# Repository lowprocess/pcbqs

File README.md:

# pcbqs

PCB DC/power-integrity analysis, magneto-quasistatic and PEEC extraction, magnetic
near fields, low-frequency S-parameters, and ngspice operational circuits with
passive copper feedback.

```sh
pip install .
python -m pcbqs.pdn --describe --json
python -m pcbqs.mqs --describe --json
python -m pcbqs.sparams board.kicad_pcb --fmin 1e3 --fmax 1e8 --out lf
python -m pcbqs.circuit --template boost > boost.json
python -m pcbqs.circuit boost.json --out result
python -m pcbqs.circuit src/pcbqs/data/wpthb_bridge.json --out wpthb               # the wpthb full bridge
```

JSON-based solving, layout/mesh export and field reconstruction work without
`mom25d` or `kicad2ems`. Install `.[kicad2ems]` to import `.kicad_pcb` files.

With kicad2ems installed the four tools are its analyses (`pcbqs/analyses.py`, the
`kicad2ems.analyses` entry points) and `pcbqs.sparams` one of its S-parameter solvers
(`kicad2ems.solvers`: `--solvers pcbqs`): `kicad2ems --check` lists them, a config keeps a
study's under `[analysis]`, and kicad2ems-gui builds each one's settings from its
options table, runs it and shows what its result folder holds: the maps as field
dumps in its Viewer, the report and the curves (`pcbqs/reports.py`) on its Results
page. The circuit examples are configs beside their models
(`circuit/examples/*.toml`), under its File > Examples > Circuits.
Install ngspice separately for operational circuits. Component models and
parasitics are explicit assumptions; footprints do not imply calibrated models.

On Python versions without a sufficiently recent Triangle wheel (including
Python 3.14), use the kicad2ems installer: its QS option builds the pinned mesher
with the floating-point flags required by Triangle's exact predicates.

The optional CPU backend is built with `pip install '.[core]'` followed by
`python -m pcbqs.core.build`. NumPy/threaded fallbacks remain available. CuPy GPU
fill is optional: select a matching CUDA/ROCm extra and `--fill-backend cupy`.
Execution controls use `PCBQS_FILL_BACKEND`, `PCBQS_FILL_THREADS`,
`PCBQS_OMP_THREADS`, `PCBQS_NO_CORE` and `PCBQS_ARCH`; general OpenMP settings
remain supported. Static-fill plugins use the `pcbqs.static_backends` entry group.

- [Quasistatic guide](docs/quasistatic.md)
- [Low-frequency S-parameters](docs/sparams.md): a board's ports from DC to a tenth of a wavelength, with the
  return current where it flows; `--solvers pcbqs` in a kicad2ems run. Its example,
  `examples/return-path/return_path.py`: what a ground via's place does to a layer change
- [Circuits](docs/circuit.md): any circuit of parts, nodes and drives, by ngspice: its parts' losses for the
  thermal analysis, its copper's currents for the fields; ten examples, each with a board whose copper can be put in, and the wpthb full bridge; KiCad boards,
  schematics and netlists read into a model
- [Temperature](docs/thermal.md): a trial of a lightweight thermal solver, on a grid and on the triangle mesh
- [Validation and limits](docs/quasistatic-validation.md)
- [Migration](docs/migration.md)
- [Copied-code provenance](PROVENANCE.json)
- [PEEC and skin-effect test PCB](examples/peec-skin/README.md): two coupons,
  model comparisons, independent references and a reproducible KiCad layout.
- [Experimental PEEC PDN comparison](examples/pdn-peec-trial/README.md):
  loaded rails, independent DC/AC references, and mesh sensitivity.
- [Jetson AGX Thor PDN check](examples/jetson-pdn/REPORT.md): a real-board DC
  cross-check, cavity limitations, and a bounded local PEEC/skin comparison.
- [PEEC memory reduction](examples/peec-memory/REPORT.md) and the
  [experimental compressed backend](docs/peec-memory.md): graded meshes,
  hierarchical current/charge operators and iterative solving.

Private `_numerics` functions are independently maintained snapshots, not a
shared library or a runtime link to MoM. `emsdev` supplies only existing hardware
and native-build services. RF/full-wave solvers remain in `mom25d`.

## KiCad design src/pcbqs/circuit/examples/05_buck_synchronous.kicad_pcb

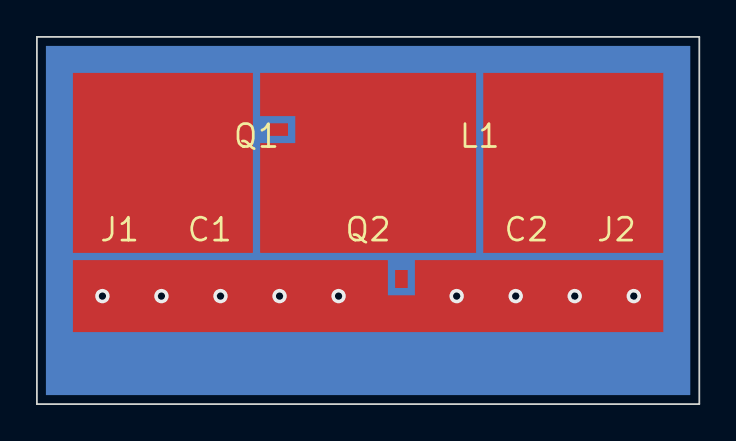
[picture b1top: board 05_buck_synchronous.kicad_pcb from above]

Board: 2 copper layers, 36.8 x 20.4 mm, 7 parts (0 on the bottom side), 4 nets, no tracks yet.

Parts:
C1: 22u; C_1210_3225Metric
C2: 47u; C_1210_3225Metric
J1: supply; SolderWirePad_1x02_SMD_3x3mm
J2: load; SolderWirePad_1x02_SMD_3x3mm
L1: 22uH; L_7.3x7.3_H4.5
Q1, Q2: MOSFET; SO-8FL_5x6mm

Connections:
GND: C1.2, C2.2, J1.2, J2.2, Q2.2 (S)
in: C1.1, J1.1, Q1.1 (D)
out: C2.1, J2.1, L1.2
sw: L1.1, Q1.2 (S), Q2.1 (D)

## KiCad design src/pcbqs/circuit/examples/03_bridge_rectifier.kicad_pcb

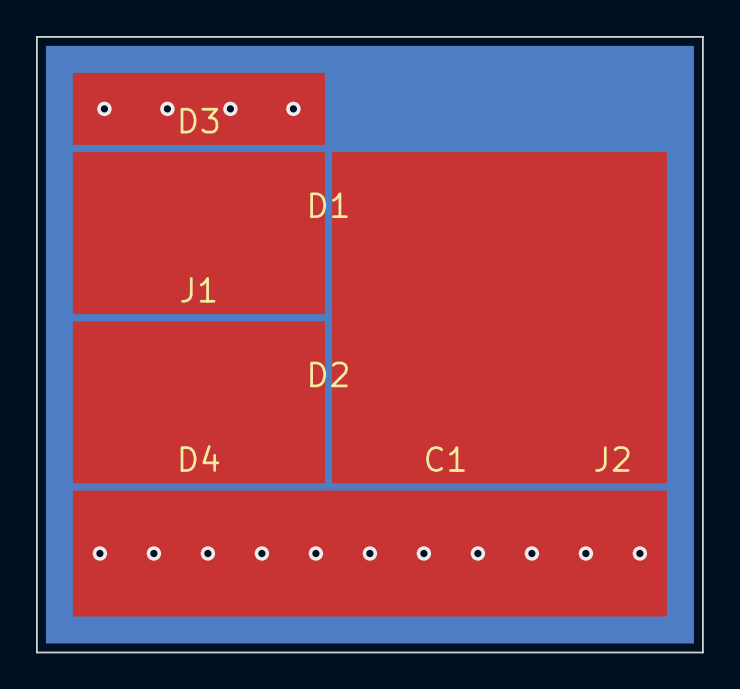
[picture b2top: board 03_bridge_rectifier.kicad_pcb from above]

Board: 2 copper layers, 37.0 x 34.2 mm, 7 parts (0 on the bottom side), 4 nets, no tracks yet.

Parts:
C1: 2.2m; CP_Elec_10x10
D1, D2, D3, D4: D; D_SMA
J1: supply; SolderWirePad_1x02_SMD_3x3mm
J2: load; SolderWirePad_1x02_SMD_3x3mm

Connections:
GND: C1.2, D3.2 (A), D4.2 (A), J2.2
l: D1.2 (A), D3.1 (K), J1.1
n: D2.2 (A), D4.1 (K), J1.2
p: C1.1, D1.1 (K), D2.1 (K), J2.1

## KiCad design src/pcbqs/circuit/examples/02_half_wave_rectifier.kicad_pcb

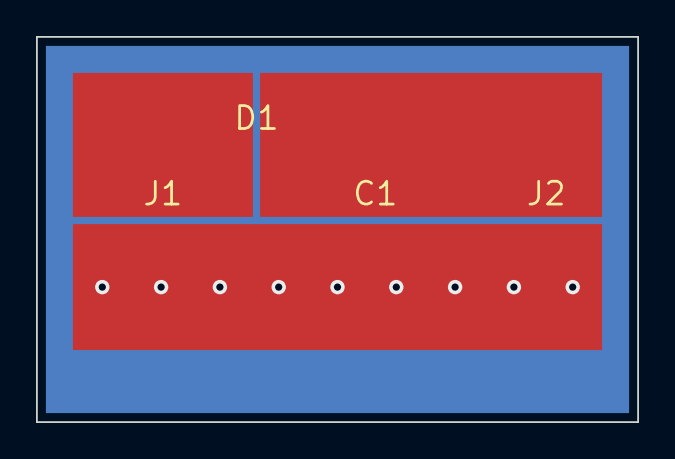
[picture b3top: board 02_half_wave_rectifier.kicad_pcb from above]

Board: 2 copper layers, 33.4 x 21.4 mm, 4 parts (0 on the bottom side), 3 nets, no tracks yet.

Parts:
C1: 1m; CP_Elec_10x10
D1: D; D_SMA
J1: supply; SolderWirePad_1x02_SMD_3x3mm
J2: load 100; SolderWirePad_1x02_SMD_3x3mm

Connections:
GND: C1.2, J1.2, J2.2
ac: D1.2 (A), J1.1
out: C1.1, D1.1 (K), J2.1

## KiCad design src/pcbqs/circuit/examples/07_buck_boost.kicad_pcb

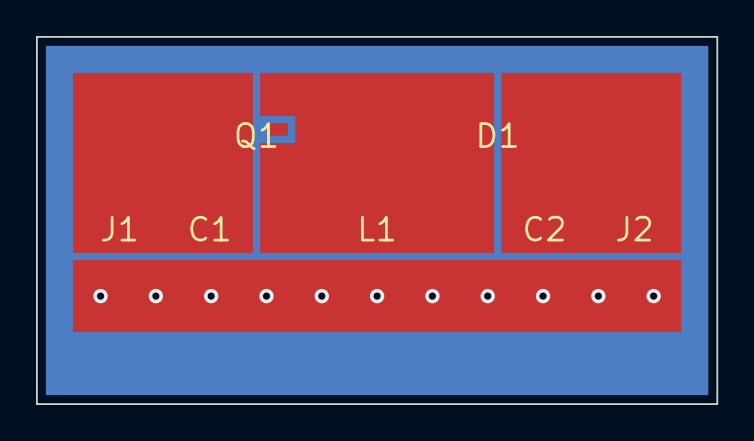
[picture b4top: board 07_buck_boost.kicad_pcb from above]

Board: 2 copper layers, 37.8 x 20.4 mm, 7 parts (0 on the bottom side), 4 nets, no tracks yet.

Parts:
C1: 22u; C_1210_3225Metric
C2: 47u; C_1210_3225Metric
D1: D; D_SMA
J1: supply; SolderWirePad_1x02_SMD_3x3mm
J2: load 30; SolderWirePad_1x02_SMD_3x3mm
L1: 47uH; L_7.3x7.3_H4.5
Q1: MOSFET; SO-8FL_5x6mm

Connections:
GND: C1.2, C2.2, J1.2, J2.2, L1.2
in: C1.1, J1.1, Q1.1 (D)
out: C2.1, D1.2 (A), J2.1
sw: D1.1 (K), L1.1, Q1.2 (S)

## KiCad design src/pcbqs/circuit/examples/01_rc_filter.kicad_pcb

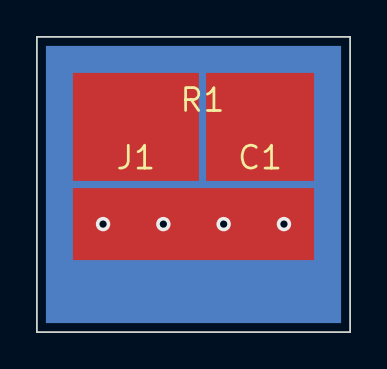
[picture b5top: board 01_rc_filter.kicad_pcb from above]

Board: 2 copper layers, 17.4 x 16.4 mm, 3 parts (0 on the bottom side), 3 nets, no tracks yet.

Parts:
C1: 100n; C_0805_2012Metric
J1: supply; SolderWirePad_1x02_SMD_3x3mm
R1: 1k; R_0805_2012Metric

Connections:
GND: C1.2, J1.2
in: J1.1, R1.1
out: C1.1, R1.2

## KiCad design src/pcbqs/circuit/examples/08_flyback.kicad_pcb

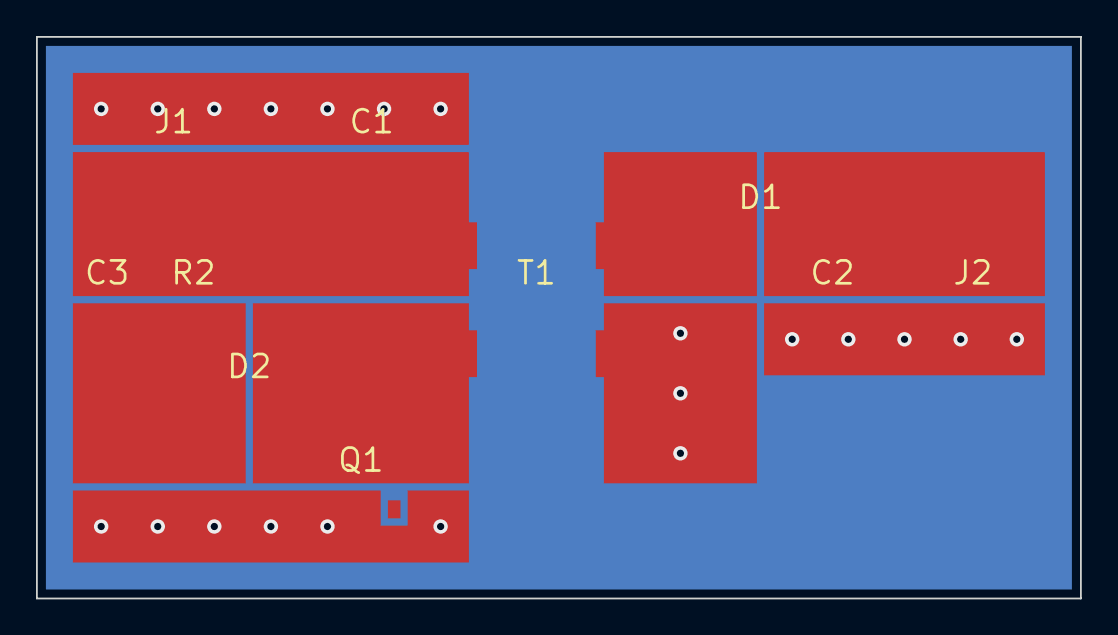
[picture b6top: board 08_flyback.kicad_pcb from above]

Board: 2 copper layers, 58.0 x 31.2 mm, 10 parts (0 on the bottom side), 6 nets, no tracks yet.

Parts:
C1: 22u; C_1210_3225Metric
C2: 100u; C_1210_3225Metric
C3: 10n; C_0805_2012Metric
D1, D2: D; D_SMA
J1: supply; SolderWirePad_1x02_SMD_3x3mm
J2: load 5; SolderWirePad_1x02_SMD_3x3mm
Q1: MOSFET; SO-8FL_5x6mm
R2: 2k; R_2512_6332Metric
T1: 200uH 2:1; Transformer_4Pad

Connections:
GND: C1.2, C2.2, J1.2, J2.2, Q1.2 (S), T1.4 (S2)
clamp: C3.1, D2.1 (K), R2.1
in: C1.1, C3.2, J1.1, R2.2, T1.1
out: C2.1, D1.1 (K), J2.1
sec: D1.2 (A), T1.3 (S1)
sw: D2.2 (A), Q1.1 (D), T1.2

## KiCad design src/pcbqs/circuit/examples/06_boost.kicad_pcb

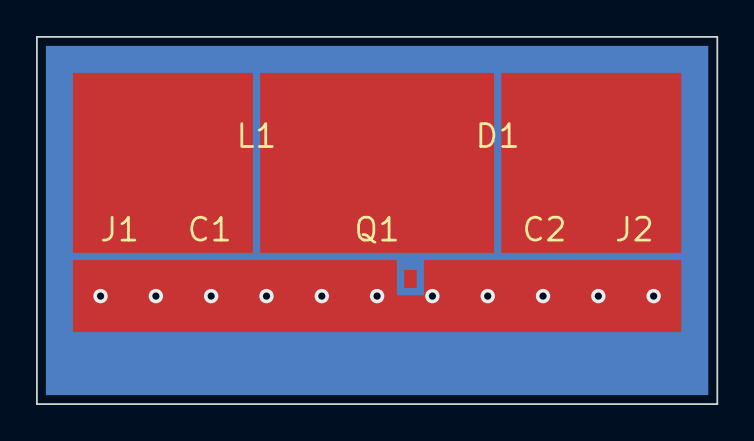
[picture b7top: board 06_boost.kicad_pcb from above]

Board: 2 copper layers, 37.8 x 20.4 mm, 7 parts (0 on the bottom side), 4 nets, no tracks yet.

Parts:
C1: 10u; C_1210_3225Metric
C2: 22u; C_1210_3225Metric
D1: D; D_SMA
J1: supply; SolderWirePad_1x02_SMD_3x3mm
J2: load 48; SolderWirePad_1x02_SMD_3x3mm
L1: 47uH; L_7.3x7.3_H4.5
Q1: MOSFET; SO-8FL_5x6mm

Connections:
GND: C1.2, C2.2, J1.2, J2.2, Q1.2 (S)
in: C1.1, J1.1, L1.1
out: C2.1, D1.1 (K), J2.1
sw: D1.2 (A), L1.2, Q1.1 (D)

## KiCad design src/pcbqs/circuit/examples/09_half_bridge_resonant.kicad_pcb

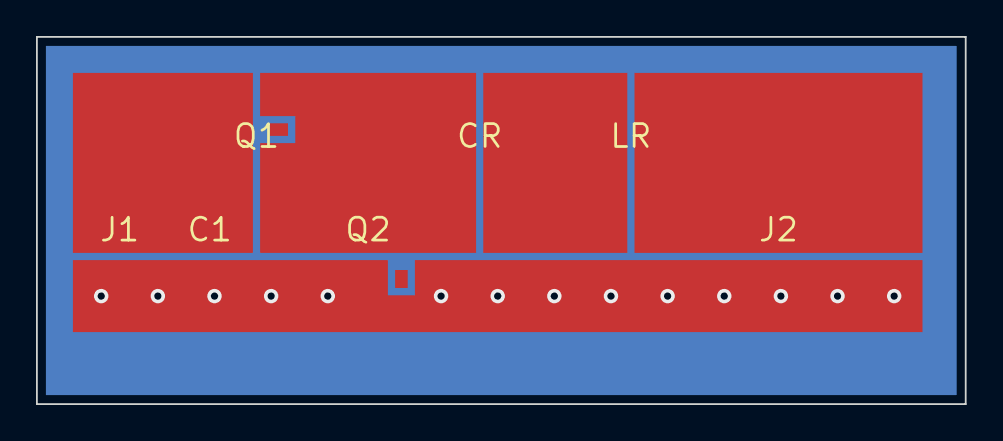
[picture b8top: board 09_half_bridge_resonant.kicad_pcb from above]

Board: 2 copper layers, 51.6 x 20.4 mm, 7 parts (0 on the bottom side), 5 nets, no tracks yet.

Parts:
C1: 47u; C_1210_3225Metric
CR: 100n; C_1210_3225Metric
J1: supply; SolderWirePad_1x02_SMD_3x3mm
J2: load 5; SolderWirePad_1x02_SMD_3x3mm
LR: 22uH; L_7.3x7.3_H4.5
Q1, Q2: MOSFET; SO-8FL_5x6mm

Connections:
GND: C1.2, J1.2, J2.2, Q2.2 (S)
a: CR.2, LR.1
b: J2.1, LR.2
in: C1.1, J1.1, Q1.1 (D)
sw: CR.1, Q1.2 (S), Q2.1 (D)
